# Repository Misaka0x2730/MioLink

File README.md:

# MioLink

This project is a port of the [Black Magic Probe project](https://github.com/blackmagic-debug/blackmagic) to Raspberry Pi RP2040 (2 Cortex-M0+ cores at 125MHz) MCU.  
The project is a USB debugger that operates via JTAG and SWD interfaces, supporting many ARM Cortex processors ([see supported device list here](https://black-magic.org/supported-targets.html)).  
It also supports debug output via Serial Wire Output (SWO) and RTT. Additionally, the device has an extra UART serial port that can be accessed through a second Virtual COM port.  
This README contains only the basic information: information about the hardware, how to build the firmware and flash the probe.  
Detailed instructions on how to use the debugger, how to configure SWO, RTT and etc. will be posted later in [the project's wiki](https://github.com/Misaka0x2730/MioLink/wiki).

# Hardware
## General information
The main board for this device is *MioLink* ([rev. A](https://github.com/Misaka0x2730/MioLink/blob/main/hardware/revA/MioLink_revA.pdf)/[rev. B](https://github.com/Misaka0x2730/MioLink/blob/main/hardware/revB/MioLink_revB.pdf)): RP2040 + 16Mbit (2MiB) QSPI Flash memory (W25Q16).  
At this moment, there are two revisions of *MioLink*: rev. A and rev. B.  
You can find information about their differences [here](https://github.com/Misaka0x2730/MioLink/wiki/MioLink-revisions-comparsion).  
[MioLink_Pico](https://github.com/Misaka0x2730/MioLink/blob/main/hardware/MioLink_Pico/revA/MioLink_Pico_revA.pdf) is a breakout board for Pico and Pico W featuring a power switch and voltage converters.  
Standard Pico and Pico W boards are also supported.  
The device type is determined at runtime, so all boards use the same firmware.  
[MioLink_adapter](https://github.com/Misaka0x2730/MioLink/blob/main/hardware/MioLink_adapter/revA/MioLink_adapter_revA.pdf) is an adapter that allows you to connect the probe with target boards that have different types of connectors.  
You can find all hardware CAD files (designed in KiCad) [here](https://github.com/Misaka0x2730/MioLink/tree/main/hardware).  

## Pinout
### MioLink and MioLink_Pico target connector pinout
*MioLink* and *MioLink_Pico* use the standard ARM 10-pin 0.1" connector and has additional 4-pin 0.1" UART connector:  

Pin | Name  | Description              | Pin | Name          | Description
:--:|:-----:|:------------------------:|:---:|:-------------:|:-----------------------------------------------------------------------:
1   | VTref | Target reference voltage | 2   | SWDIO/TMS     | SWD Data input/output / JTAG Test mode select
3   | GND   | Ground                   | 4   | SWDCLK/TCK    | SWD Clock / JTAG Test clock
5   | GND   | Ground                   | 6   | SWO/TDO/RX    | SWO Trace output / JTAG Test data output / UART Probe RX (Target TX)
7   | NC    | Not connected            | 8   | NC/TDI/TX     | Not connected for SWD / JTAG Test data input / UART Probe TX (Target RX)
9   | GND   | Ground                   | 10  | RESET         | Reset pin

#### UART connector pinout:

Pin | Name | Description                    | Pin | Name  | Description
:--:|:----:|:------------------------------:|:---:|:-----:|:------------------------:
1   | RX   | UART Probe RX (UART Target TX) | 2   | VTref | Target reference voltage
3   | TX   | UART Probe TX (UART Target RX) | 4   | GND   | Ground

### Pico/Pico W pinout

Pin       | Name       | Description
:--------:|:----------:|:------------------------------------------------------------------------:
10 (GP7)  | RESET      | Reset pin
11 (GP8)  | TX         | UART Probe TX (UART Target RX)
12 (GP9)  | RX         | UART Probe RX (UART Target TX)
13        | GND        | Ground
14 (GP10) | SWDCLK/TCK | SWD Clock / JTAG Test clock
15 (GP11) | SWDIO/TMS  | SWD Data input/output / JTAG Test mode select
16 (GP12) | NC/TDI/TX  | Not connected for SWD / JTAG Test data input / UART Probe TX (Target RX)
17 (GP13) | SWO/TDO/RX | SWO Trace output / JTAG Test data output / UART Probe RX (Target TX)
36        | 3V3        | 3.3V output from Pico

## Connecting target to probe
### Information about the Vtref pin (pin 1)
PLEASE, note that the Vtref pin (pin 1) on *MioLink* and *MioLink_Pico* MUST always be connected (internally or externally) to the logic level voltage of the target being debugged (from 1.65V to 5.5V) to power the level shifters inside the probe.  
If the target device operates at a 3.3V logic level, this pin can be powered internally by the probe, also in this case, the target can be powered by the probe if needed, and the maximum current is specified in the table below, but be careful, accidentally connecting anything to this pin that is not rated for 3.3V may lead to irreversible damage to the external device.  
3.3V power supply on this pin can be enabled with the GDB command ```monitor tpwr enable``` and disabled with the command ```monitor tpwr disable```. By default (after probe reset), it's disabled.  
Pico and Pico W are also able to provide 3.3V power for target, but it is recommended to keep the load on this pin less than 300mA, for more information see chapter 2.1, page 8 in [Pico datasheet](https://datasheets.raspberrypi.com/pico/pico-datasheet.pdf) and chapter 2.1, page 9 in [Pico W datasheet](https://datasheets.raspberrypi.com/picow/pico-w-datasheet.pdf).  
In all other cases, the Vtref pin (pin 1) functions as an input and must be connected to the logic level voltage of the target device.  
The allowable voltage range is from 1.65V to 5.5V.  

#### Maximum output current of the Vtref pin (pin 1):

Board | Max current
:----:|:----------:
MioLink | rev.A: ~200 mA;  rev.B: ~350 mA (min. 300, max. 400)
MioLink_Pico | ~200 mA (min. 175, max. 234)
Pico or Pico W | ~300 mA from 3V3 pin,  see recommendations in  Pico and Pico W datasheets.

### JTAG pins description

Pin | Description
:----:|:----------:
Vtref | Target reference voltage
GND   | Ground
TMS   | Test mode select
TCK   | Test clock
TDO   | Test data output
TDI   | Test data input
RESET | Optional reset pin

### SWD pins description

Pin    | Description
:-----:|:----------:
Vtref  | Target reference voltage
GND    | Ground
SWDIO  | Data input/output
SWDCLK | Clock signal
RESET  | Optional reset pin

# Building and flashing the probe
## Requirements
The following tools are required to build this project:
- git
- make
- Python
- cmake
- gcc
- arm-none-eabi-gcc

## Install all requirements on Windows
The simplest way to build the firmware under Windows environment is to use MinGW64.

Build steps:
1. Download and install [MSYS2](https://www.msys2.org/);
2. Run mingw64;
3. Upgrade packets, MinGW64 will be restarted:  ```pacman -Syu```
4. Install all requirements:  ```pacman -S git mingw-w64-x86_64-python mingw-w64-x86_64-make mingw-w64-x86_64-cmake mingw-w64-x86_64-arm-none-eabi-gcc mingw-w64-x86_64-gcc```
5. Clone this project with submodules:  ```git clone --recurse-submodules https://github.com/Misaka0x2730/MioLink.git```
6. Change current dir:  ```cd MioLink/firmware```

## Install all requirements on Ubuntu
1. Download and install all requirements:
```
cd /opt
sudo wget "https://developer.arm.com/-/media/Files/downloads/gnu/13.3.rel1/binrel/arm-gnu-toolchain-13.3.rel1-x86_64-arm-none-eabi.tar.xz"
sudo tar -xf arm-gnu-toolchain-13.3.rel1-x86_64-arm-none-eabi.tar.xz
sudo rm arm-gnu-toolchain-13.3.rel1-x86_64-arm-none-eabi.tar.xz
echo 'export PATH="$PATH":/opt/arm-gnu-toolchain-13.3.rel1-x86_64-arm-none-eabi/bin' >> ~/.bashrc
sudo apt-get install git python3 cmake
```
2. Clone this project with submodules into home directory:
```
cd ~
git clone --recurse-submodules https://github.com/Misaka0x2730/MioLink.git
```
3. Change current dir:  ```cd MioLink/firmware```

## Build debug image:
1. Create working directory:  ```mkdir debug```
2. Go to working directory:  ```cd debug```
3. Run cmake:  ```cmake -DCMAKE_BUILD_TYPE=Debug -G "MinGW Makefiles" ..```
4. Build image:  ```cmake --build .```
5. Use ```MioLink.uf2``` to flash device via factory USB-MSC bootloader.

## Build release image:
1. Create working directory:  ```mkdir release```
2. Go to working directory:  ```cd release```
3. Run cmake:  ```cmake -DCMAKE_BUILD_TYPE=Release -G "MinGW Makefiles" ..```
4. Build image:  ```cmake --build .```
5. Use ```MioLink.uf2``` to flash device via factory USB-MSC bootloader.

## How to flash the probe
1. Disconnect USB cable;
2. Press BOOT (BOOTSEL on Pico and Pico W) button;
3. Connect USB cable to PC;
4. Release BOOT (BOOTSEL on Pico and Pico W) button;
5. Drag-and-Drop ```MioLink.uf2``` file to mass storage device;
6. The device will be flashed and rebooted automatically, after which it is ready for use.

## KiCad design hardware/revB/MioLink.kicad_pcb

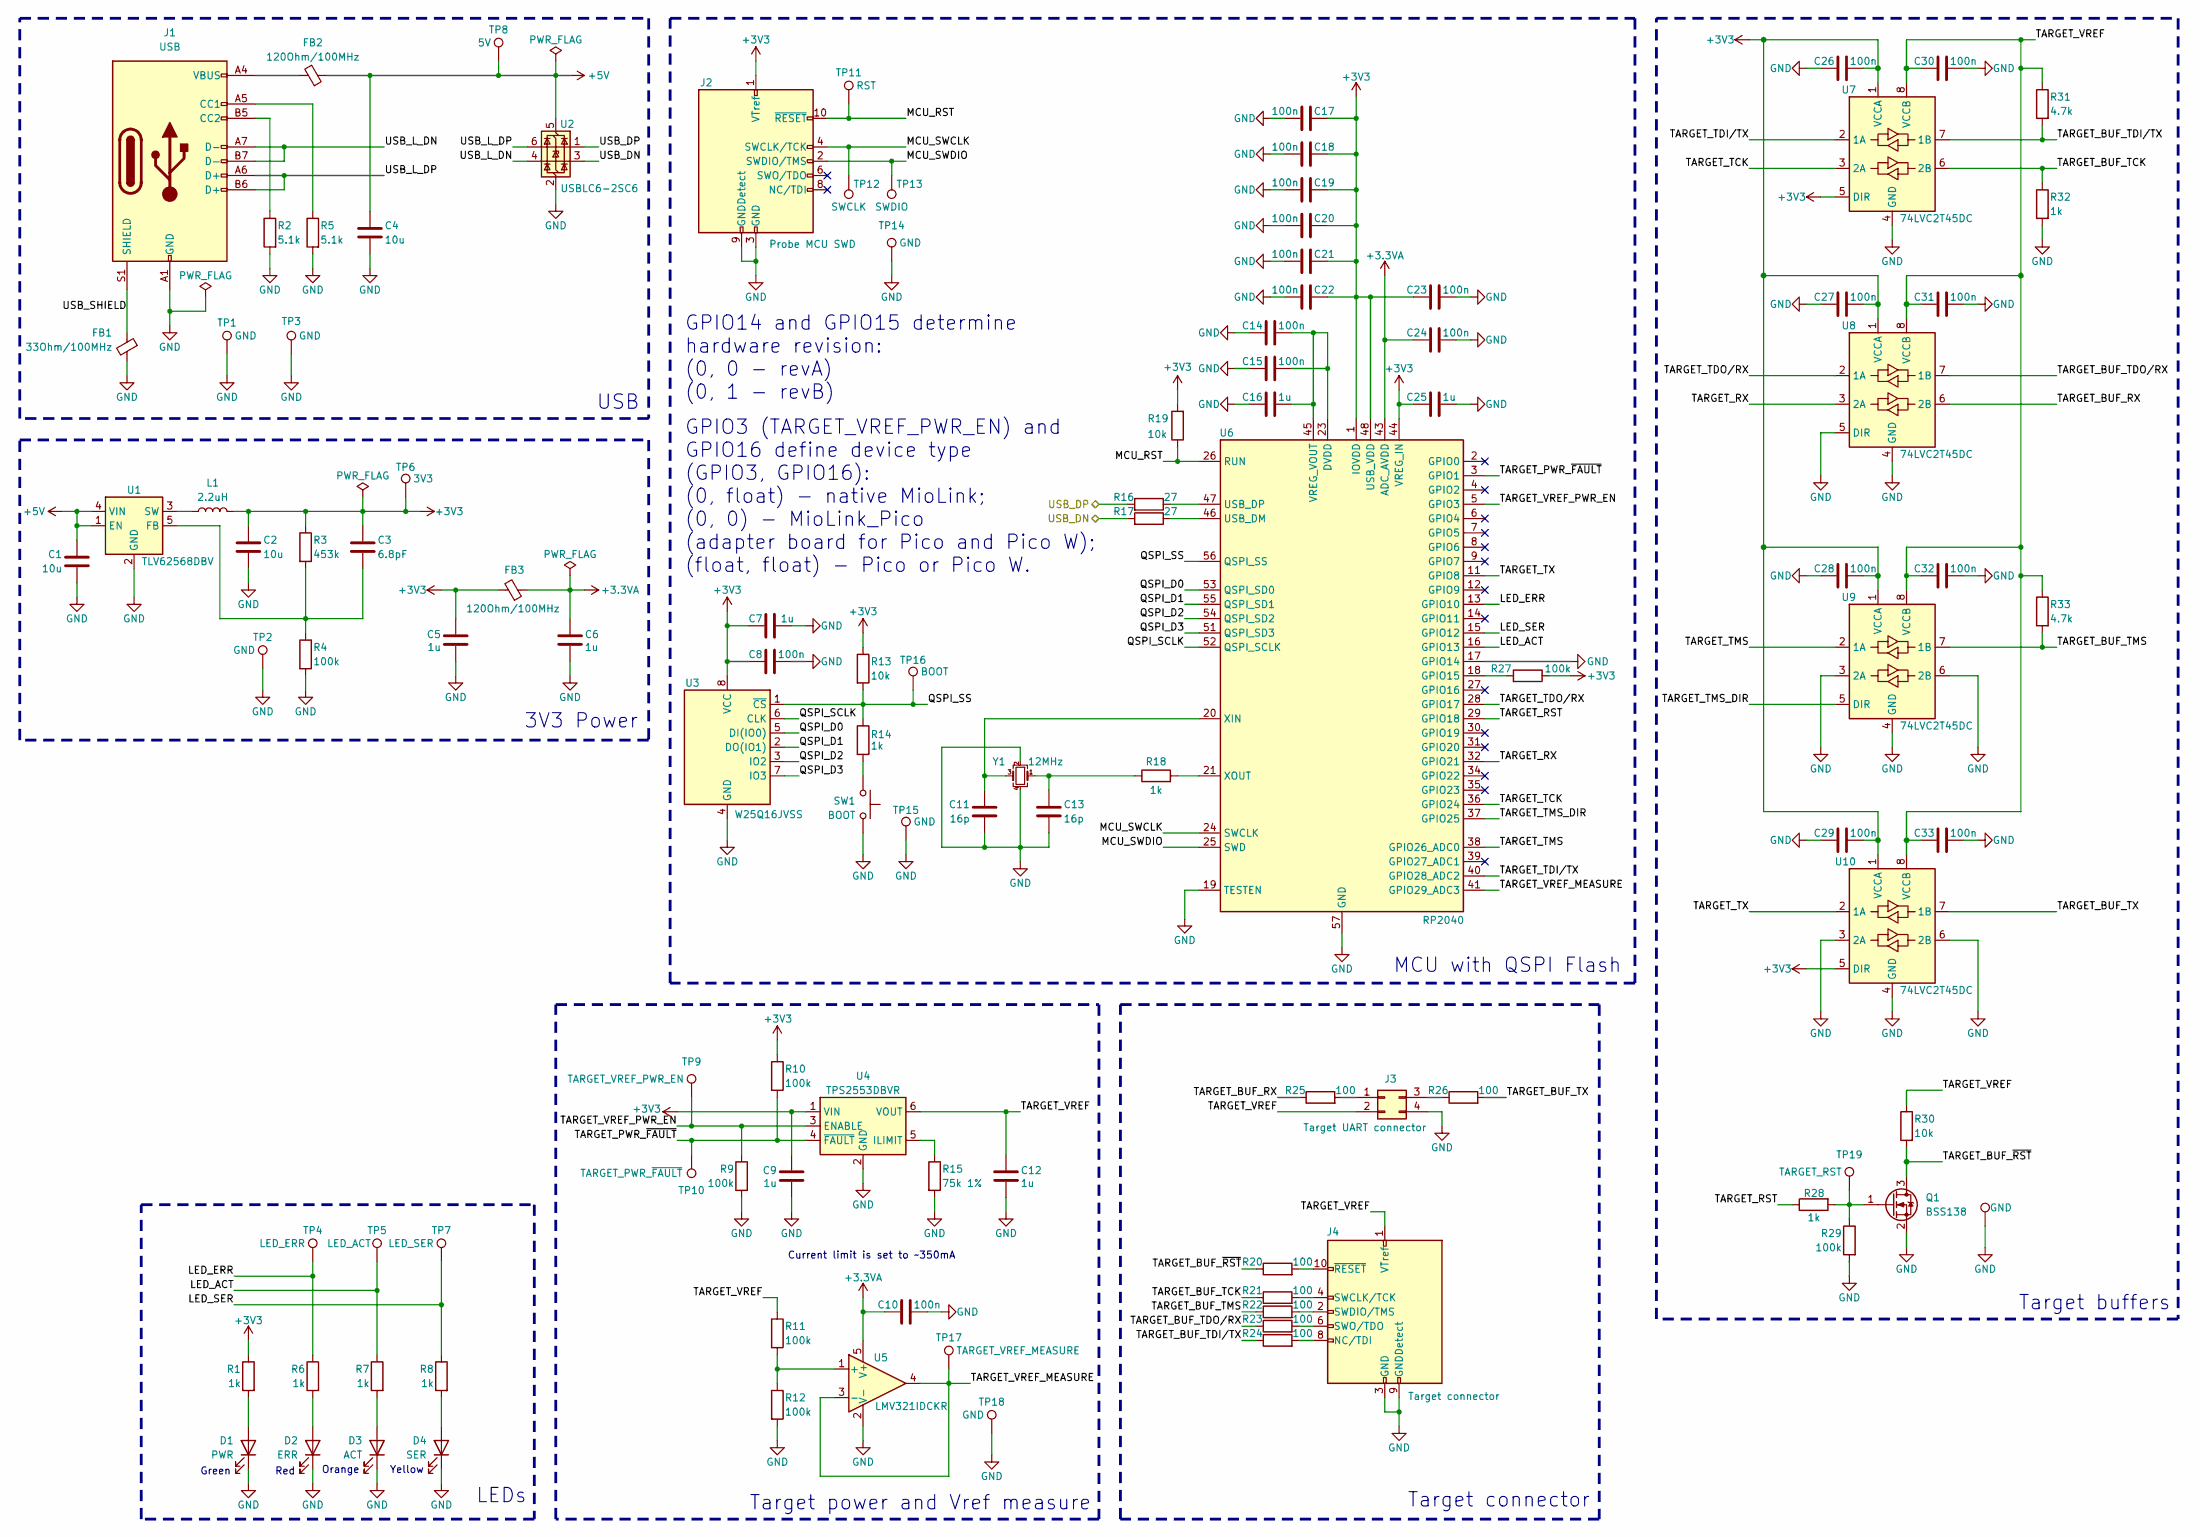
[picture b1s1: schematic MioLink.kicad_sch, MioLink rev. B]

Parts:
C1, C2, C4: 10u; C_0603_1608Metric; Part Number CL10A106KP8NNNC; LCSC C19702
C3: 6.8pF; C_0402_1005Metric; Part Number CC0402CRNPO9BN6R8; LCSC C189470
C5, C6, C7, C9, C12, C16, C25: 1u; C_0402_1005Metric; Part Number CL05A105KA5NQNC; LCSC C52923
C8, C10, C14, C15, C17, C18, C19, C20, C21, C22, C23, C24, C26, C27, C28, C29, C30, C31, C32, C33: 100n; C_0402_1005Metric; Part Number CL05B104KO5NNNC; LCSC C1525
C11, C13: 16p; C_0402_1005Metric; Part Number CC0402JRNPO9BN160; LCSC C77590
D1: PWR; LED_1206_3216Metric; Part Number XL-3216SYGC; LCSC C965826
D2: ERR; LED_1206_3216Metric; Part Number XL-3216SURC; LCSC C965822
D3: ACT; LED_1206_3216Metric; Part Number XL-3216UOC; LCSC C965823
D4: SER; LED_1206_3216Metric; Part Number XL-3216UYC; LCSC C965824
FB1: 33Ohm/100MHz; L_0603_1608Metric; Part Number BLM18PG330SN1D; LCSC C88984
FB2, FB3: 120Ohm/100MHz; L_0603_1608Metric; Part Number BLM18PG121SN1D; LCSC C14709
J1: USB; USB_C_Receptacle_HRO_TYPE-C-31-M-12; Part Number TYPE-C-31-M-12A; LCSC C5337088
J2: Probe MCU SWD; PinHeader_2x05_P1.27mm_Vertical_SMD; Part Number 20021121-00010T4LF; LCSC C598540
J3: Target UART connector; PinHeader_2x02_P2.54mm_Horizontal; Part Number PZ254-2-02-W-8.5; LCSC C2894982
J4: Target connector; IDC-Header_2x05_P2.54mm_Horizontal; Part Number 0502A001A1BC; LCSC C7434504
L1: 2.2uH; L_Taiyo-Yuden_NR-30xx; Part Number LPS3015-222MRC; LCSC C2844756
Q1: BSS138; SOT-23; Part Number BSS138LT1G; LCSC C82045
R1, R6, R7, R8, R14, R18, R28, R32: 1k; R_0402_1005Metric; Part Number 0402WGF1001TCE; LCSC C11702
R2, R5: 5.1k; R_0402_1005Metric; Part Number 0402WGF5101TCE; LCSC C25905
R3: 453k; R_0402_1005Metric; Part Number AC0402FR-07453KL; LCSC C27009
R4, R9, R10, R11, R12, R27, R29: 100k; R_0402_1005Metric; Part Number 0402WGF1003TCE; LCSC C25741
R13, R19, R30: 10k; R_0402_1005Metric; Part Number 0402WGF1002TCE; LCSC C25744
R15: 75k 1%; R_0402_1005Metric; Part Number 0402WGF7502TCE; LCSC C25798
R16, R17: 27; R_0402_1005Metric; Part Number 0402WGF270JTCE; LCSC C25100
R20, R21, R22, R23, R24, R25, R26: 100; R_0402_1005Metric; Part Number 0402WGF1000TCE; LCSC C25076
R31, R33: 4.7k; R_0402_1005Metric; Part Number 0402WGF4701TCE; LCSC C25900
SW1: BOOT; SW_SPST_B3S-1000; Part Number B3S-1000; LCSC C2733655
TP1, TP2, TP14, TP15, TP18, TP20: GND; TestPoint_Pad_D1.0mm
TP3: GND; TestPoint_Keystone_5000-5004_Miniature
TP4: LED_ERR; TestPoint_Pad_D1.0mm
TP5: LED_ACT; TestPoint_Pad_D1.0mm
TP6: 3V3; TestPoint_Pad_D1.0mm
TP7: LED_SER; TestPoint_Pad_D1.0mm
TP8: 5V; TestPoint_Pad_D1.0mm
TP9: TARGET_VREF_PWR_EN; TestPoint_Pad_D1.0mm
TP10: TARGET_PWR_~{FAULT}; TestPoint_Pad_D1.0mm
TP11: RST; TestPoint_Pad_D1.0mm
TP12: SWCLK; TestPoint_Pad_D1.0mm
TP13: SWDIO; TestPoint_Pad_D1.0mm
TP16: BOOT; TestPoint_Pad_D1.0mm
TP17: TARGET_VREF_MEASURE; TestPoint_Pad_D1.0mm
TP19: TARGET_RST; TestPoint_Pad_D1.0mm
U1: TLV62568DBV; SOT-23-5; Part Number TLV62568DBV; LCSC C163219
U2: USBLC6-2SC6; SOT-23-6; Part Number USBLC6-2SC6; LCSC C7519
U3: W25Q16JVSS; SOIC-8_5.23x5.23mm_P1.27mm; Part Number W25Q16JVSSIQ; LCSC C82317
U4: TPS2553DBVR; SOT-23-6; Part Number TPS2553DBV; LCSC C55266
U5: LMV321IDCKR; SOT-353_SC-70-5; Part Number LMV321IDCKR; LCSC C3029047
U6: RP2040; QFN-56-1EP_7x7mm_P0.4mm_EP3.2x3.2mm; Part Number RP2040; LCSC C2040
U7, U8, U9, U10: 74LVC2T45DC; VSSOP-8_2.3x2mm_P0.5mm; Part Number SN74LVC2T45DCU; LCSC C22356905
Y1: 12MHz; Crystal_SMD_3225-4Pin_3.2x2.5mm; Part Number ABM8-272-T3; LCSC C20625731

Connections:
+3.3VA: C6.1, C10.1, C24.1, FB3.1, U5.5 (V+), U6.43 (ADC_AVDD)
+3V3: C2.1, C3.1, C5.1, C7.1, C8.1, C9.1, C17.1, C18.1, C19.1, C20.1, C21.1, C22.1, C23.1, C25.1, C26.1, C27.1, C28.1, C29.1, FB3.2, J2.1 (VTref), L1.2, R1.1, R3.1, R10.1, R13.1, R19.2, R27.1, TP6.1, U3.8 (VCC), U4.1 (VIN), U6.1 (IOVDD), U6.10 (IOVDD), U6.22 (IOVDD), U6.33 (IOVDD), U6.42 (IOVDD), U6.44 (VREG_IN), U6.48 (USB_VDD), U6.49 (IOVDD), U7.1 (VCCA), U7.5 (DIR), U8.1 (VCCA), U9.1 (VCCA), U10.1 (VCCA), U10.5 (DIR)
+5V: C1.2, C4.1, FB2.1, TP8.1, U1.1 (EN), U1.4 (VIN), U2.5 (VBUS)
/LED_ACT: R7.1, TP5.1, U6.16 (GPIO13)
/LED_ERR: R6.1, TP4.1, U6.13 (GPIO10)
/LED_SER: R8.1, TP7.1, U6.15 (GPIO12)
/MCU_RST: J2.10 (~RESET), R19.1, TP11.1, U6.26 (RUN)
/MCU_SWCLK: J2.4 (SWCLK/TCK), TP12.1, U6.24 (SWCLK)
/MCU_SWDIO: J2.2 (SWDIO/TMS), TP13.1, U6.25 (SWD)
/QSPI_D0: U3.5 (DI(IO0)), U6.53 (QSPI_SD0)
/QSPI_D1: U3.2 (DO(IO1)), U6.55 (QSPI_SD1)
/QSPI_D2: U3.3 (IO2), U6.54 (QSPI_SD2)
/QSPI_D3: U3.7 (IO3), U6.51 (QSPI_SD3)
/QSPI_SCLK: U3.6 (CLK), U6.52 (QSPI_SCLK)
/QSPI_SS: R13.2, R14.1, TP16.1, U3.1 (~CS), U6.56 (QSPI_SS)
/TARGET_BUF_RX: R25.1, U8.6 (2B)
/TARGET_BUF_TCK: R21.1, R32.1, U7.6 (2B)
/TARGET_BUF_TDI/TX: R24.1, R31.2, U7.7 (1B)
/TARGET_BUF_TDO/RX: R23.1, U8.7 (1B)
/TARGET_BUF_TMS: R22.1, R33.2, U9.7 (1B)
/TARGET_BUF_TX: R26.2, U10.7 (1B)
/TARGET_BUF_~RST: Q1.3 (D), R20.1, R30.2
/TARGET_PWR_~FAULT: R10.2, TP10.1, U4.4 (~FAULT), U6.3 (GPIO1)
/TARGET_RST: R28.1, U6.29 (GPIO18)
/TARGET_RX: U6.32 (GPIO21), U8.3 (2A)
/TARGET_TCK: U6.36 (GPIO24), U7.3 (2A)
/TARGET_TDI/TX: U6.40 (GPIO28_ADC2), U7.2 (1A)
/TARGET_TDO/RX: U6.28 (GPIO17), U8.2 (1A)
/TARGET_TMS: U6.38 (GPIO26_ADC0), U9.2 (1A)
/TARGET_TMS_DIR: U6.37 (GPIO25), U9.5 (DIR)
/TARGET_TX: U6.11 (GPIO8), U10.2 (1A)
/TARGET_VREF: C12.1, C30.2, C31.2, C32.2, C33.2, J3.2, J4.1 (VTref), R11.1, R30.1, R31.1, R33.1, U4.6 (VOUT), U7.8 (VCCB), U8.8 (VCCB), U9.8 (VCCB), U10.8 (VCCB)
/TARGET_VREF_MEASURE: TP17.1, U5.3 (-), U5.4, U6.41 (GPIO29_ADC3)
/TARGET_VREF_PWR_EN: R9.1, TP9.1, U4.3 (ENABLE), U6.5 (GPIO3)
/USB_DN: R17.2, U2.3 (I/O2)
/USB_DP: R16.2, U2.1 (I/O1)
/USB_L_DN: J1.A7 (D-), J1.B7 (D-), U2.4 (I/O2)
/USB_L_DP: J1.A6 (D+), J1.B6 (D+), U2.6 (I/O1)
/USB_SHIELD: FB1.1, J1.S1 (SHIELD)
GND: C1.1, C2.2, C4.2, C5.2, C6.2, C7.2, C8.2, C9.2, C10.2, C11.2, C12.2, C13.2, C14.1, C15.1, C16.1, C17.2, C18.2, C19.2, C20.2, C21.2, C22.2, C23.2, C24.2, C25.2, C26.2, C27.2, C28.2, C29.2, C30.1, C31.1, C32.1, C33.1, D1.1 (K), D2.1 (K), D3.1 (K), D4.1 (K), FB1.2, J1.A1 (GND), J1.A12 (GND), J1.B1 (GND), J1.B12 (GND), J2.3 (GND), J2.5 (GND), J2.9 (GNDDetect), J3.4, J4.3 (GND), J4.5 (GND), J4.9 (GNDDetect), Q1.2 (S), R2.2, R4.2, R5.2, R9.2, R12.2, R15.2, R29.2, R32.2, SW1.1, TP1.1, TP2.1, TP3.1, TP14.1, TP15.1, TP18.1, TP20.1, U1.2 (GND), U2.2 (GND), U3.4 (GND), U4.2 (GND), U5.2 (V-), U6.17 (GPIO14), U6.19 (TESTEN), U6.57 (GND), U7.4 (GND), U8.4 (GND), U8.5 (DIR), U9.3 (2A), U9.4 (GND), U9.6 (2B), U10.3 (2A), U10.4 (GND), U10.6 (2B), Y1.2, Y1.4
unnamed: C13.1, R18.1, Y1.1
unnamed: D1.2 (A), R1.2
unnamed: D2.2 (A), R6.2
unnamed: D3.2 (A), R7.2
unnamed: D4.2 (A), R8.2
unnamed: FB2.2, J1.A4 (VBUS), J1.A9 (VBUS), J1.B4 (VBUS), J1.B9 (VBUS)
unnamed: J1.A5 (CC1), R5.1
unnamed: J1.B5 (CC2), R2.1
unnamed: J3.1, R25.2
unnamed: J3.3, R26.1
unnamed: J4.8 (NC/TDI), R24.2
unnamed: J4.4 (SWCLK/TCK), R21.2
unnamed: J4.2 (SWDIO/TMS), R22.2
unnamed: J4.6 (SWO/TDO), R23.2
unnamed: J4.10 (~RESET), R20.2
unnamed: Q1.1 (G), R28.2, R29.1, TP19.1
unnamed: R14.2, SW1.2
unnamed: C3.2, R3.2, R4.1, U1.5 (FB)
unnamed: L1.1, U1.3 (SW)
unnamed: R15.1, U4.5 (ILIMIT)
unnamed: R11.2, R12.1, U5.1 (+)
unnamed: R27.2, U6.18 (GPIO15)
unnamed: R17.1, U6.46 (USB_DM)
unnamed: R16.1, U6.47 (USB_DP)
unnamed: C14.2, C15.2, C16.2, U6.23 (DVDD), U6.45 (VREG_VOUT), U6.50 (DVDD)
unnamed: C11.1, U6.20 (XIN), Y1.3
unnamed: R18.2, U6.21 (XOUT)

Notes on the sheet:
Red
GPIO3 (TARGET_VREF_PWR_EN) and GPIO16 define device type (GPIO3, GPIO16): (0, float) - native MioLink; (0, 0) - MioLink_Pico (adapter board for Pico and Pico W); (float, float) - Pico or Pico W.
Target buffers
Current limit is set to ~350mA
Yellow
3V3 Power
MCU with QSPI Flash
Green
GPIO14 and GPIO15 determine hardware revision: (0, 0 - revA) (0, 1 - revB)
Target power and Vref measure
Orange
Target connector
LEDs
USB

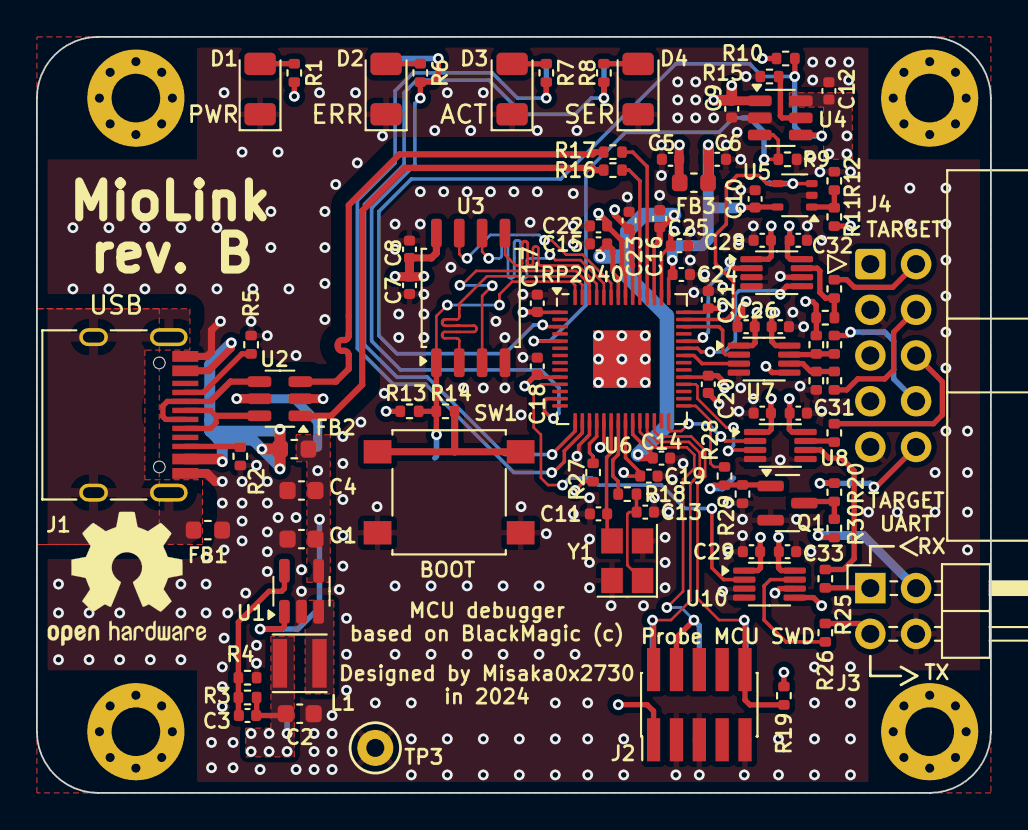
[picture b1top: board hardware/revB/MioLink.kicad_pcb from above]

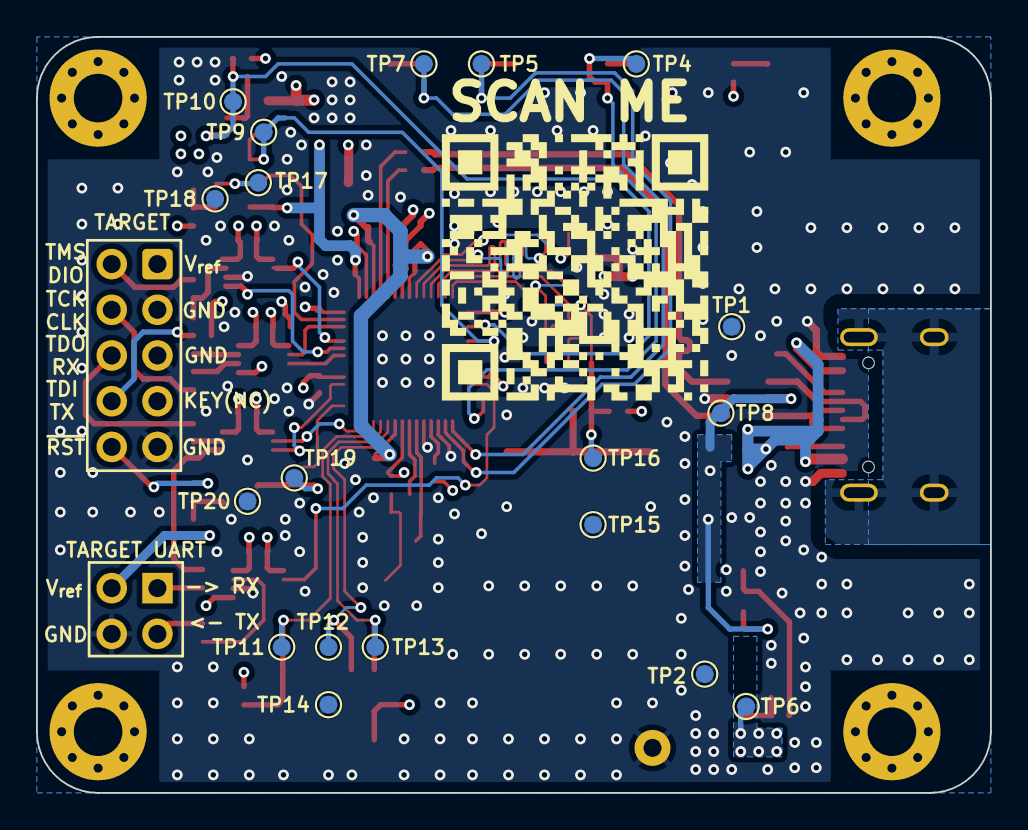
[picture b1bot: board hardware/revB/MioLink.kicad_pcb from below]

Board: 4 copper layers, 53.0 x 42.0 mm, 117 parts (20 on the bottom side), 67 nets.

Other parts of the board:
G1: LOGO
REF1, REF2, REF3, REF4: MountingHole_2.7mm_M2.5_Pad_Via
REF5: OSHW-Logo2_9.8x8mm_SilkScreen

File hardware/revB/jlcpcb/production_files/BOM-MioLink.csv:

Comment,Designator,Footprint,LCSC
1k,"R1,R14,R18,R28,R32,R6,R7,R8",R_0402_1005Metric,C11702
120Ohm/100MHz,"FB2,FB3",L_0603_1608Metric,C14709
100n,"C10,C14,C15,C17,C18,C19,C20,C21,C22,C23,C24,C26,C27,C28,C29,C30,C31,C32,C33,C8",C_0402_1005Metric,C1525
TLV62568DBV,U1,SOT-23-5,C163219
6.8pF,C3,C_0402_1005Metric,C189470
10u,"C1,C2,C4",C_0603_1608Metric,C19702
RP2040,U6,QFN-56-1EP_7x7mm_P0.4mm_EP3.2x3.2mm,C2040
12MHz,Y1,Crystal_SMD_3225-4Pin_3.2x2.5mm,C20625731
74LVC2T45DC,"U10,U7,U8,U9",VSSOP-8_2.3x2mm_P0.5mm,C22356905
100,"R20,R21,R22,R23,R24,R25,R26",R_0402_1005Metric,C25076
27,"R16,R17",R_0402_1005Metric,C25100
100k,"R10,R11,R12,R27,R29,R4,R9",R_0402_1005Metric,C25741
10k,"R13,R19,R30",R_0402_1005Metric,C25744
75k 1%,R15,R_0402_1005Metric,C25798
4.7k,"R31,R33",R_0402_1005Metric,C25900
5.1k,"R2,R5",R_0402_1005Metric,C25905
453k,R3,R_0402_1005Metric,C27009
BOOT,SW1,SW_SPST_B3S-1000,C2733655
2.2uH,L1,L_Taiyo-Yuden_NR-30xx,C2844756
Target UART connector,J3,PinHeader_2x02_P2.54mm_Horizontal,C2894982
LMV321IDCKR,U5,SOT-353_SC-70-5,C3029047
1u,"C12,C16,C25,C5,C6,C7,C9",C_0402_1005Metric,C52923
USB,J1,USB_C_Receptacle_HRO_TYPE-C-31-M-12,C5337088
TPS2553DBVR,U4,SOT-23-6,C55266
Probe MCU SWD,J2,PinHeader_2x05_P1.27mm_Vertical_SMD,C598540
Target connector,J4,IDC-Header_2x05_P2.54mm_Horizontal,C7434504
USBLC6-2SC6,U2,SOT-23-6,C7519
16p,"C11,C13",C_0402_1005Metric,C77590
BSS138,Q1,SOT-23,C82045
W25Q16JVSS,U3,SOIC-8_5.23x5.23mm_P1.27mm,C82317
33Ohm/100MHz,FB1,L_0603_1608Metric,C88984
ERR,D2,LED_1206_3216Metric,C965822
ACT,D3,LED_1206_3216Metric,C965823
SER,D4,LED_1206_3216Metric,C965824
PWR,D1,LED_1206_3216Metric,C965826
GND,TP3,TestPoint_Keystone_5000-5004_Miniature,
TARGET_VREF_PWR_EN,TP9,TestPoint_Pad_D1.0mm,
SWCLK,TP12,TestPoint_Pad_D1.0mm,
TARGET_PWR_~{FAULT},TP10,TestPoint_Pad_D1.0mm,
GND,TP2,TestPoint_Pad_D1.0mm,
GND,TP20,TestPoint_Pad_D1.0mm,
GND,TP15,TestPoint_Pad_D1.0mm,
5V,TP8,TestPoint_Pad_D1.0mm,
LED_SER,TP7,TestPoint_Pad_D1.0mm,
GND,TP1,TestPoint_Pad_D1.0mm,
3V3,TP6,TestPoint_Pad_D1.0mm,
GND,TP18,TestPoint_Pad_D1.0mm,
BOOT,TP16,TestPoint_Pad_D1.0mm,
TARGET_RST,TP19,TestPoint_Pad_D1.0mm,
GND,TP14,TestPoint_Pad_D1.0mm,
LED_ERR,TP4,TestPoint_Pad_D1.0mm,
LED_ACT,TP5,TestPoint_Pad_D1.0mm,
RST,TP11,TestPoint_Pad_D1.0mm,
TARGET_VREF_MEASURE,TP17,TestPoint_Pad_D1.0mm,
SWDIO,TP13,TestPoint_Pad_D1.0mm,

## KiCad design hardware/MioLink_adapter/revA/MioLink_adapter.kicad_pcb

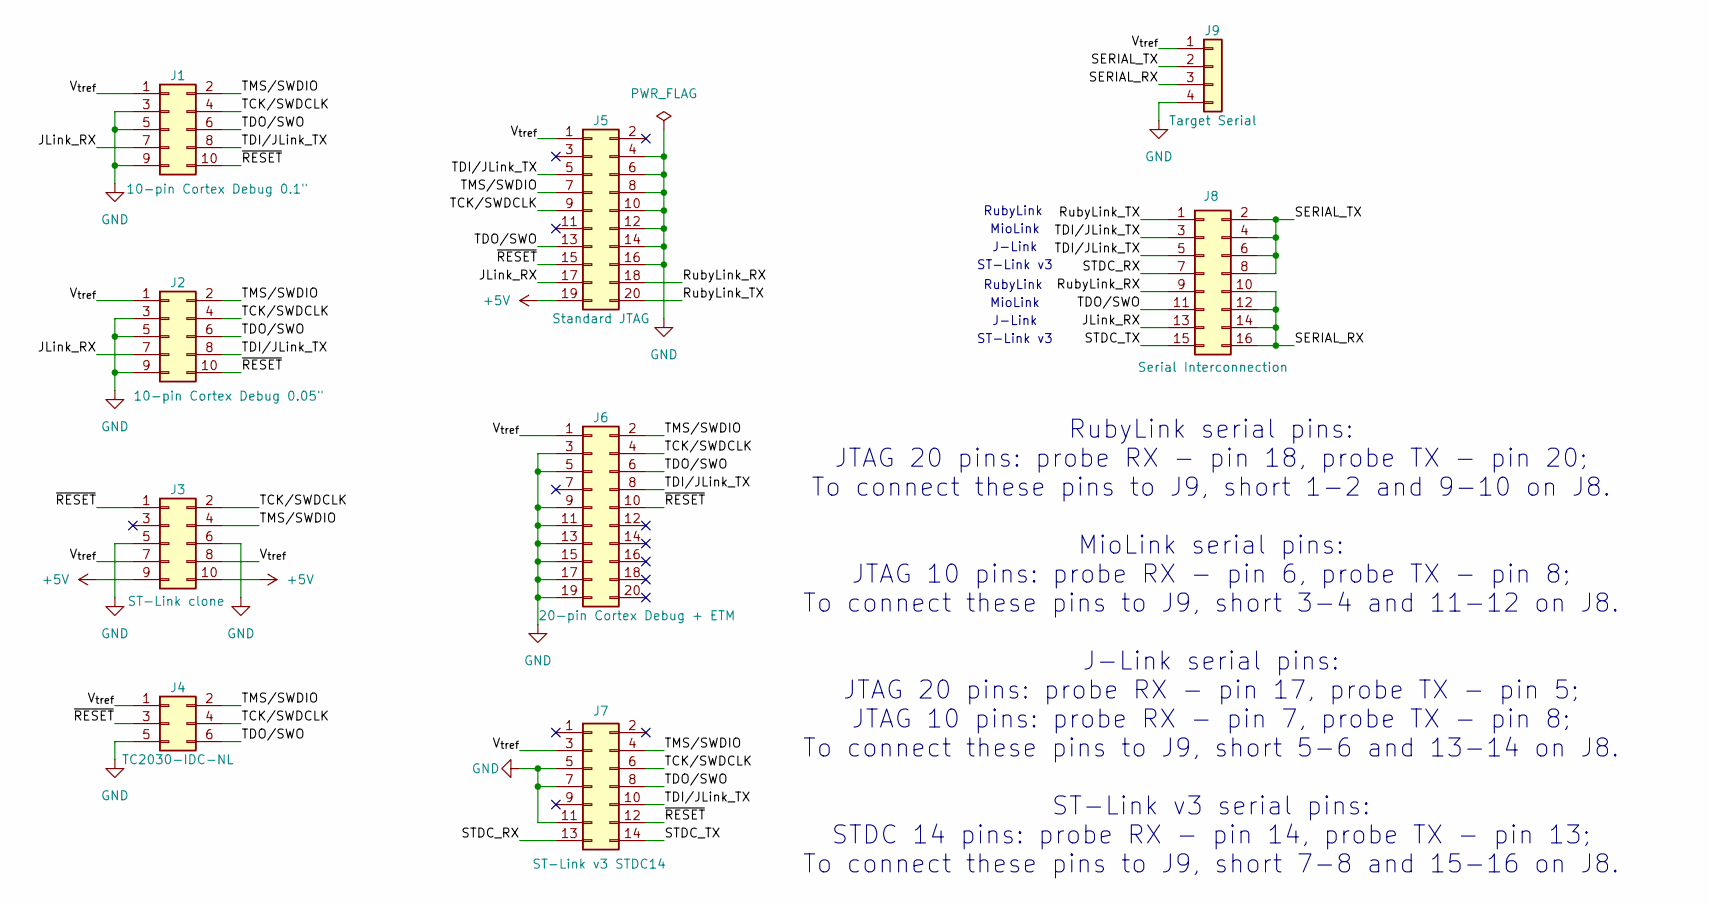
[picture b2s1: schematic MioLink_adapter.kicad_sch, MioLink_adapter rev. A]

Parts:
J1: 10-pin Cortex Debug 0.1"; IDC-Header_2x05_P2.54mm_Vertical
J2: 10-pin Cortex Debug 0.05"; PinHeader_2x05_P1.27mm_Vertical_SMD
J3: ST-Link clone; IDC-Header_2x05_P2.54mm_Vertical
J4: TC2030-IDC-NL; PinHeader_2x03_P2.54mm_Vertical
J5: Standard JTAG; IDC-Header_2x10_P2.54mm_Vertical
J6: 20-pin Cortex Debug + ETM; PinHeader_2x10_P1.27mm_Vertical_SMD
J7: ST-Link v3 STDC14; PinHeader_2x07_P1.27mm_Vertical_SMD
J8: Serial Interconnection; PinHeader_2x08_P2.54mm_Vertical
J9: Target Serial; PinHeader_1x04_P2.54mm_Horizontal

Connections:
+5V: J3.9, J3.10, J5.19
/JLink_RX: J1.7, J2.7, J5.17, J8.13
/RubyLink_RX: J5.18, J8.9
/RubyLink_TX: J5.20, J8.1
/SERIAL_RX: J8.10, J8.12, J8.14, J8.16, J9.3
/SERIAL_TX: J8.2, J8.4, J8.6, J8.8, J9.2
/STDC_RX: J7.13, J8.7
/STDC_TX: J7.14, J8.15
/TCK/SWDCLK: J1.4, J2.4, J3.2, J4.4, J5.9, J6.4, J7.6
/TDI/JLink_TX: J1.8, J2.8, J5.5, J6.8, J7.10, J8.3, J8.5
/TDO/SWO: J1.6, J2.6, J4.6, J5.13, J6.6, J7.8, J8.11
/TMS/SWDIO: J1.2, J2.2, J3.4, J4.2, J5.7, J6.2, J7.4
/V_{tref}: J1.1, J2.1, J3.7, J3.8, J4.1, J5.1, J6.1, J7.3, J9.1
/~RESET: J1.10, J2.10, J3.1, J4.3, J5.15, J6.10, J7.12
GND: J1.3, J1.5, J1.9, J2.3, J2.5, J2.9, J3.5, J3.6, J4.5, J5.4, J5.6, J5.8, J5.10, J5.12, J5.14, J5.16, J6.3, J6.5, J6.9, J6.11, J6.13, J6.15, J6.17, J6.19, J7.5, J7.7, J7.11, J9.4

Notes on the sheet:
MioLink
ST-Link v3
RubyLink
J-Link
RubyLink serial pins: JTAG 20 pins: probe RX - pin 18, probe TX - pin 20; To connect these pins to J9, short 1-2 and 9-10 on J8. MioLink serial pins: JTAG 10 pins: probe RX - pin 6, probe TX - pin 8; To connect these pins to J9, short 3-4 and 11-12 on J8. J-Link serial pins: JTAG 20 pins: probe RX 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

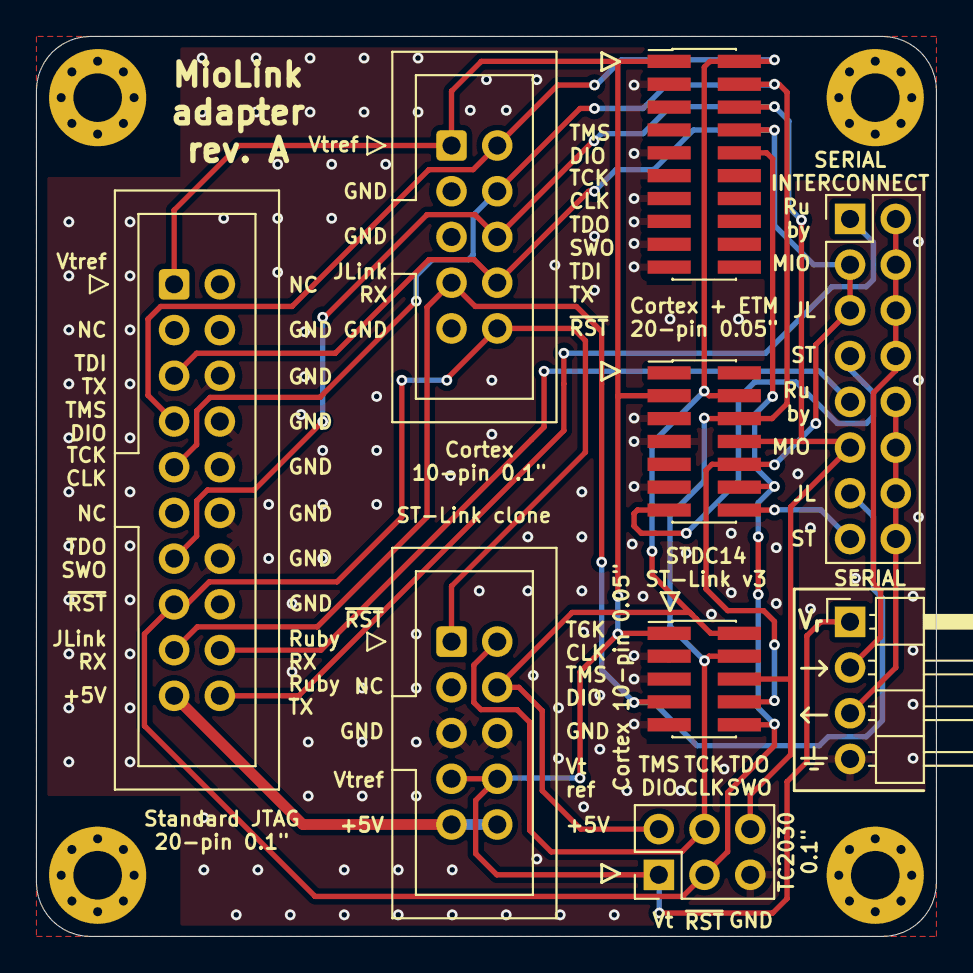
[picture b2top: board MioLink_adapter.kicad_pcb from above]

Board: 2 copper layers, 50.0 x 50.0 mm, 13 parts (0 on the bottom side), 15 nets.

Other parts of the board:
REF1, REF2, REF3, REF4: MountingHole_2.7mm_M2.5_Pad_Via

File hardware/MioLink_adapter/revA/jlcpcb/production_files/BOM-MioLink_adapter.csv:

Comment,Designator,Footprint,LCSC
TC2030-IDC-NL,J4,PinHeader_2x03_P2.54mm_Vertical,
"10-pin Cortex Debug 0.05""",J2,PinHeader_2x05_P1.27mm_Vertical_SMD,
ST-Link v3 STDC14,J7,PinHeader_2x07_P1.27mm_Vertical_SMD,
ST-Link clone,J3,IDC-Header_2x05_P2.54mm_Vertical,
"10-pin Cortex Debug 0.1""",J1,IDC-Header_2x05_P2.54mm_Vertical,
Standard JTAG,J5,IDC-Header_2x10_P2.54mm_Vertical,
Serial Interconnection,J8,PinHeader_2x08_P2.54mm_Vertical,
20-pin Cortex Debug + ETM,J6,PinHeader_2x10_P1.27mm_Vertical_SMD,
Target Serial,J9,PinHeader_1x04_P2.54mm_Horizontal,
